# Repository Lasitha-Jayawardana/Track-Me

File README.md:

# Track-Me
Real Time GPS Tracking System for SLTC Shuttle service. (Arduino + Web)

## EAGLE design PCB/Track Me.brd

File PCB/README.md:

# PCB 

## Gerber File 
	Aptinex Gerber file is used.

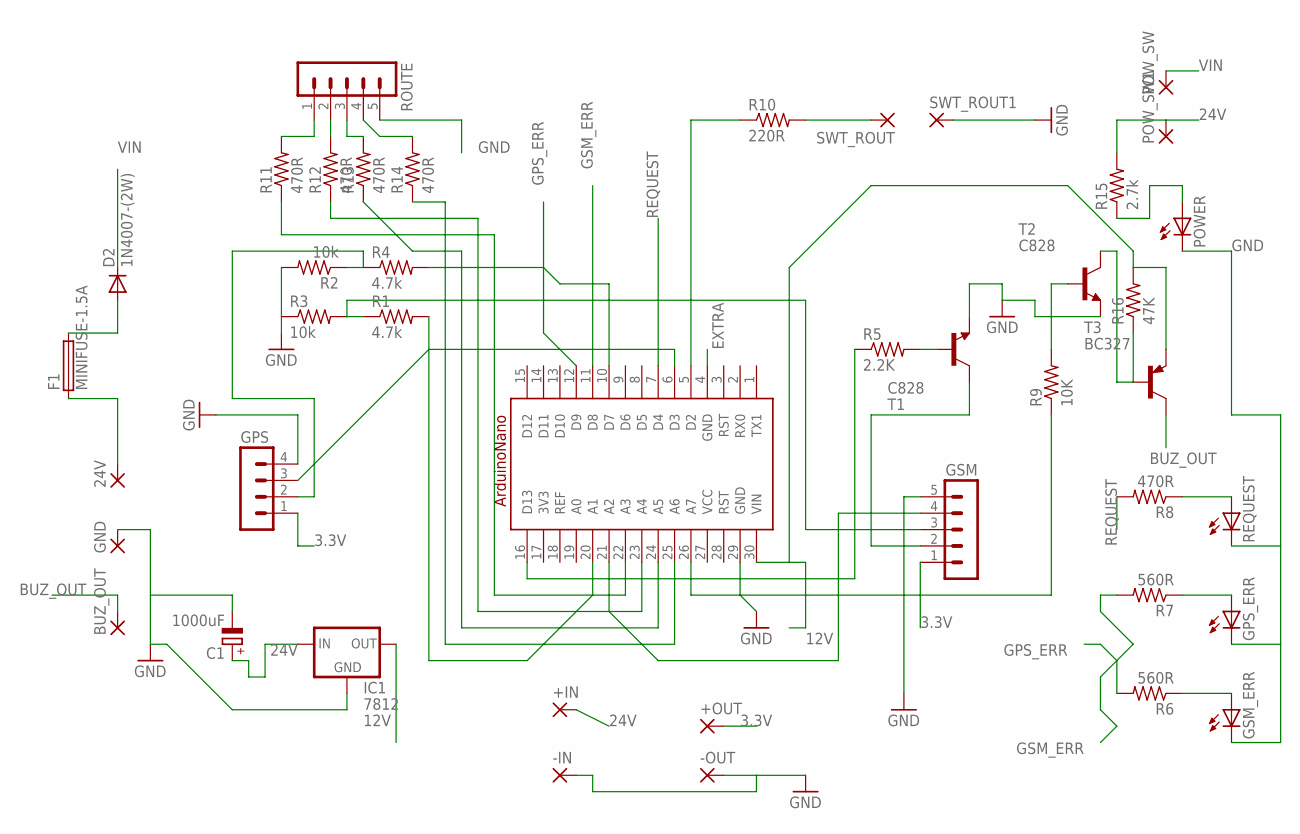
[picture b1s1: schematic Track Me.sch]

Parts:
24V: 2,54/1,1
+IN: 3,17/1,3
+OUT: 3,17/1,3
-IN: 3,17/1,3
-OUT: 3,17/1,3
A1: ARDUINONANO
BUZ_OUT: 2,54/1,1
C1: 1000uF; E5-10,5
D2: 1N4007-(2W); DO35-7
F1: MINIFUSE-1.5A; PICOFUSE
GND: 2,54/1,1
GPS: MA04-1
GPS_ERR: LED3MM
GSM: MA05-1
GSM_ERR: LED3MM
IC1: 7812; 78MXXS
POWER: LED3MM
POW_SW, POW_SW1: 2,54/1,1
R1, R4: 4.7k; 0207/7
R2, R3: 10k; 0207/7
R5: 2.2K; 0207/7
R6, R7: 560R; 0207/7
R8, R11, R12, R13, R14: 470R; 0207/7
R9: 10K; 0207/7
R10: 220R; 0207/7
R15: 2.7k; 0207/7
R16: 47K; 0207/7
REQUEST: LED3MM
ROUTE: MA05-1
SWT_ROUT, SWT_ROUT1: 2,54/1,1
T1, T2: C828; TO92-ECB
T3: BC327; TO92-EBC

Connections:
3.3V: +OUT.1, GPS.1, GSM.1
3V3: A1.17 (3V3)
12V: A1.30 (VIN), IC1.OUT, R16.2, T3.E
24V: +IN.1, C1.+, IC1.IN, POW_SW1.1, R15.2
BUZ_OUT: BUZ_OUT.1, T3.C
EXTRA: A1.4 (GND)
GND: -IN.1, -OUT.1, A1.29 (GND), C1.-, GND.1, GPS.4, GPS_ERR.K (C), GSM.5, GSM_ERR.K (C), IC1.GND, POWER.K (C), R2.2, R3.1, REQUEST.K (C), ROUTE.5, SWT_ROUT1.1, T1.E, T2.E
GPS_ERR: A1.12 (D9), R6.2
GSM_ERR: A1.11 (D8), R7.2
unnamed: GPS.2, R2.1, R4.1
unnamed: POWER.A, R15.1
unnamed: GSM.3, R1.1, R3.2
unnamed: A1.10 (D7), R4.2
unnamed: A1.6 (D3), GPS.3
unnamed: D2.A, F1.2
unnamed: R11.2, ROUTE.1
unnamed: R5.2, T1.B
unnamed: A1.16 (D13), R5.1
unnamed: R10.2, SWT_ROUT.1
unnamed: A1.20 (A1), R1.2
unnamed: A1.21 (A2), GSM.4
unnamed: R9.2, T2.B
unnamed: R8.1, REQUEST.A
unnamed: GPS_ERR.A, R7.1
unnamed: 24V.1, F1.1
unnamed: GSM.2, T1.C
unnamed: A1.5 (D2), R10.1
unnamed: GSM_ERR.A, R6.1
unnamed: A1.26 (A7), R9.1
unnamed: R12.2, ROUTE.2
unnamed: R13.2, ROUTE.3
unnamed: R14.2, ROUTE.4
unnamed: A1.22 (A3), R11.1
unnamed: A1.23 (A4), R12.1
unnamed: A1.24 (A5), R13.1
unnamed: A1.25 (A6), R14.1
unnamed: R16.1, T2.C, T3.B
REF: A1.18 (REF)
REQUEST: A1.7 (D4), R8.2
VCC: A1.27 (VCC)
VIN: D2.C, POW_SW.1

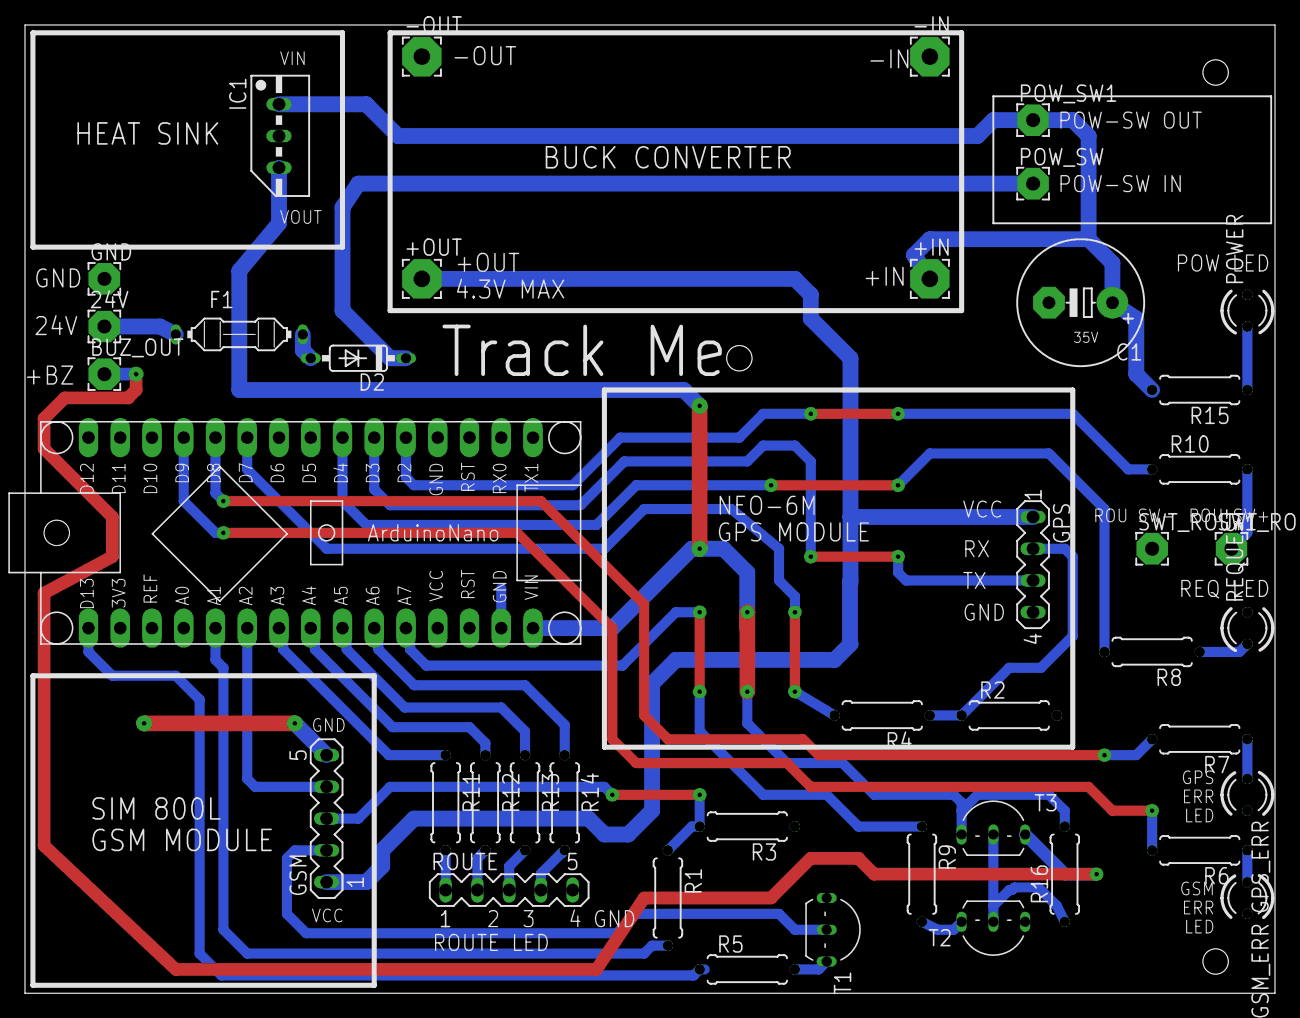
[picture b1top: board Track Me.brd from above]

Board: 2 copper layers, 100.0 x 77.5 mm, 42 parts (0 on the bottom side), 37 nets.

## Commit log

2021-03-06 Test SMS file added.
2021-03-06 Settings variables added in arduino source code.
2021-03-07 Android poject files added.
2021-03-17 Upload.php database connection error was fixed.
2021-08-15 change arduino algorithm
2021-08-15 add pcb img
